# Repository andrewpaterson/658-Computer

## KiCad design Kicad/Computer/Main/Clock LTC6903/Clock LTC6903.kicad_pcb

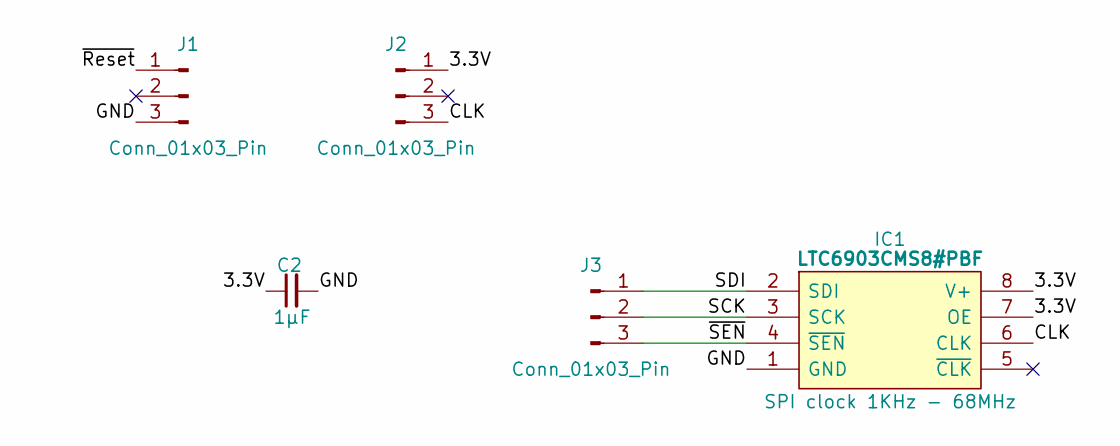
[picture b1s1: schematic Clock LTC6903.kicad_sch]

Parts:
C2: 1μF; C_0805
IC1: LTC6903CMS8#PBF; SOP65P490X110-8N; Manufacturer_Part_Number LTC6903CMS8#PBF
J1, J2, J3: Conn_01x03_Pin; PinHeader_1x03_P2.54mm_Vertical

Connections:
/3.3V: C2.1, IC1.7 (OE), IC1.8 (V+), J2.1
/CLK: IC1.6 (CLK), J2.3
/GND: C2.2, IC1.1 (GND), J1.3
/SCK: IC1.3 (SCK), J3.2
/SDI: IC1.2 (SDI), J3.1
/~Reset: J1.1
/~SEN: IC1.4 (~SEN), J3.3

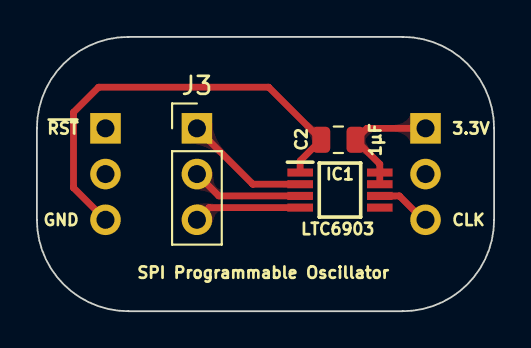
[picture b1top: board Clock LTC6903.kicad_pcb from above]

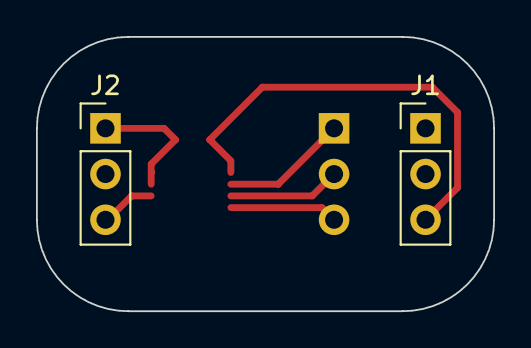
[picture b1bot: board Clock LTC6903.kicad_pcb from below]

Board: 2 copper layers, 25.4 x 15.2 mm, 5 parts (2 on the bottom side), 6 nets.

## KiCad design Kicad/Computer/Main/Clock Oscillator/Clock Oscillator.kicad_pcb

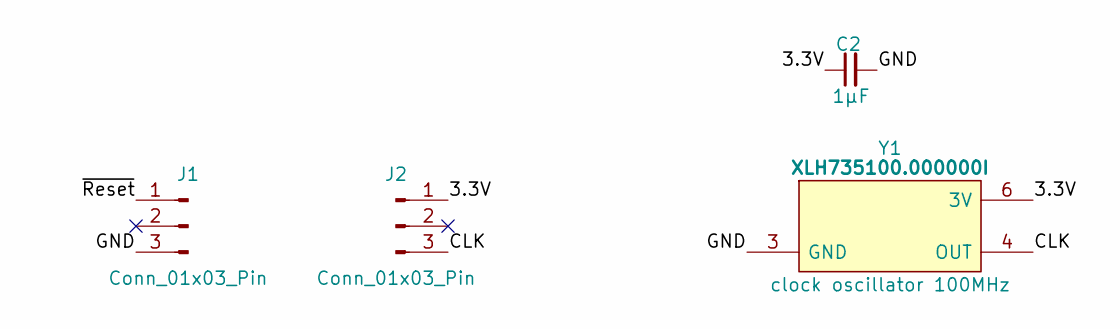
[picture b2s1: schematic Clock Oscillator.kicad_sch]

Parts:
C2: 1μF; C_0805
J1, J2: Conn_01x03_Pin; PinHeader_1x03_P2.54mm_Vertical
Y1: XLH735100.000000I; XLH735100000000I; Mouser Part Number 972-XLH735100000000I

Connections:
/3.3V: C2.1, J2.1, Y1.6 (3V)
/CLK: J2.3, Y1.4 (OUT)
/GND: C2.2, J1.3, Y1.3 (GND)
/~Reset: J1.1

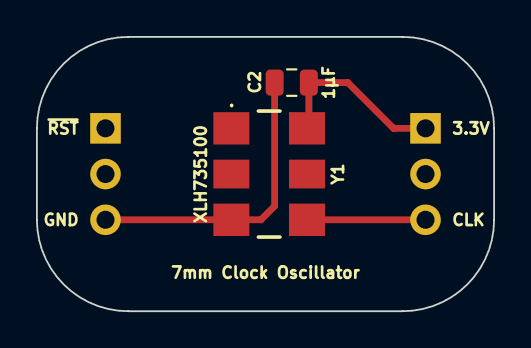
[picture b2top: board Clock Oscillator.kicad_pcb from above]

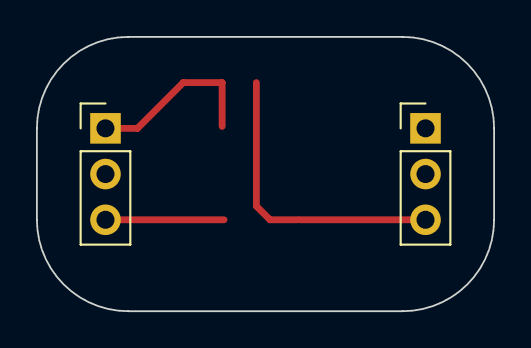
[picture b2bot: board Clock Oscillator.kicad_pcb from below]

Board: 2 copper layers, 25.4 x 15.2 mm, 4 parts (2 on the bottom side), 3 nets.

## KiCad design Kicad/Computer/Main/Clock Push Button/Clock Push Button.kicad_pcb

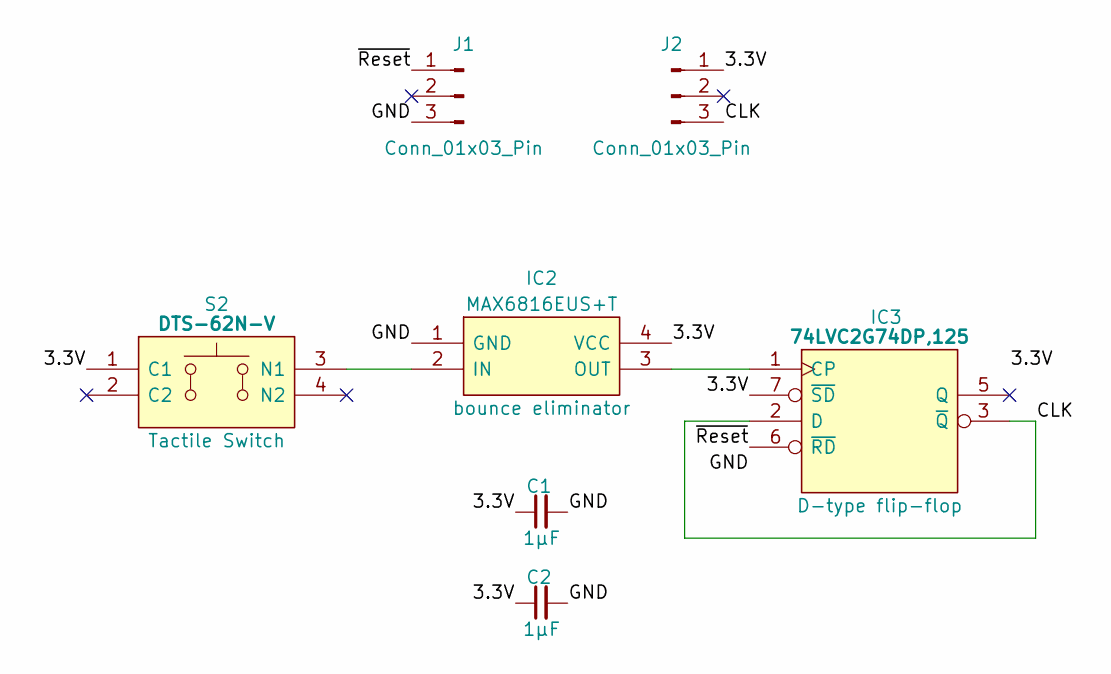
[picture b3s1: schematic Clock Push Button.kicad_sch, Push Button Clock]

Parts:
C1, C2: 1μF; C_0805
IC2: MAX6816EUS+T; MAX812REUST; Manufacturer_Part_Number MAX6816EUS+T; Mouser Part Number 700-MAX6816EUST
IC3: 74LVC2G74DP,125; SOP65P400X110-8N; Manufacturer_Part_Number 74LVC2G74DP,125; Mouser Part Number 771-74LVC2G74DP-G
J1, J2: Conn_01x03_Pin; PinHeader_1x03_P2.54mm_Vertical
S2: DTS-62N-V; DTS62NV; Manufacturer_Part_Number DTS-62N-V; Mouser Part Number 113-DTS-62N-V

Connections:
/3.3V: C1.1, C2.1, IC2.4 (VCC), IC3.7 (~SD), IC3.8 (3V), J2.1, S2.1 (C1)
/CLK: IC3.2 (D), IC3.3 (~Q), J2.3
/GND: C1.2, C2.2, IC2.1 (GND), IC3.4 (GND), J1.3
/~Reset: IC3.6 (~RD), J1.1
unnamed: IC2.2 (IN), S2.3 (N1)
unnamed: IC2.3 (OUT), IC3.1 (CP)

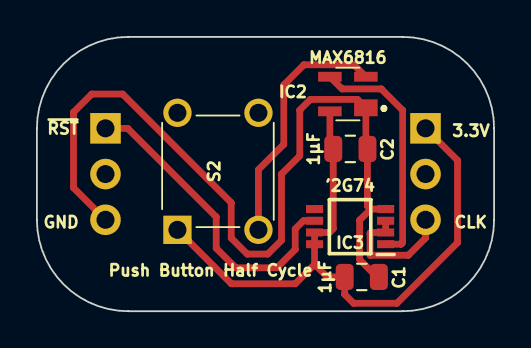
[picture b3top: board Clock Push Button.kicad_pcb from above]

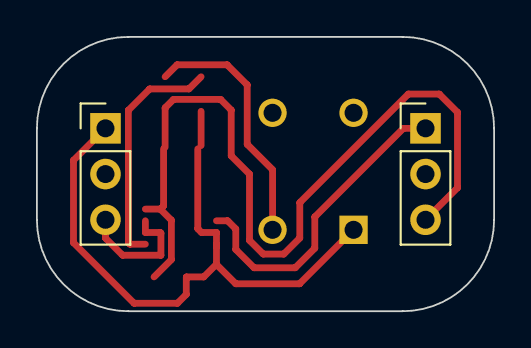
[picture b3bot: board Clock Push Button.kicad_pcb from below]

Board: 2 copper layers, 25.4 x 15.2 mm, 7 parts (2 on the bottom side), 6 nets.

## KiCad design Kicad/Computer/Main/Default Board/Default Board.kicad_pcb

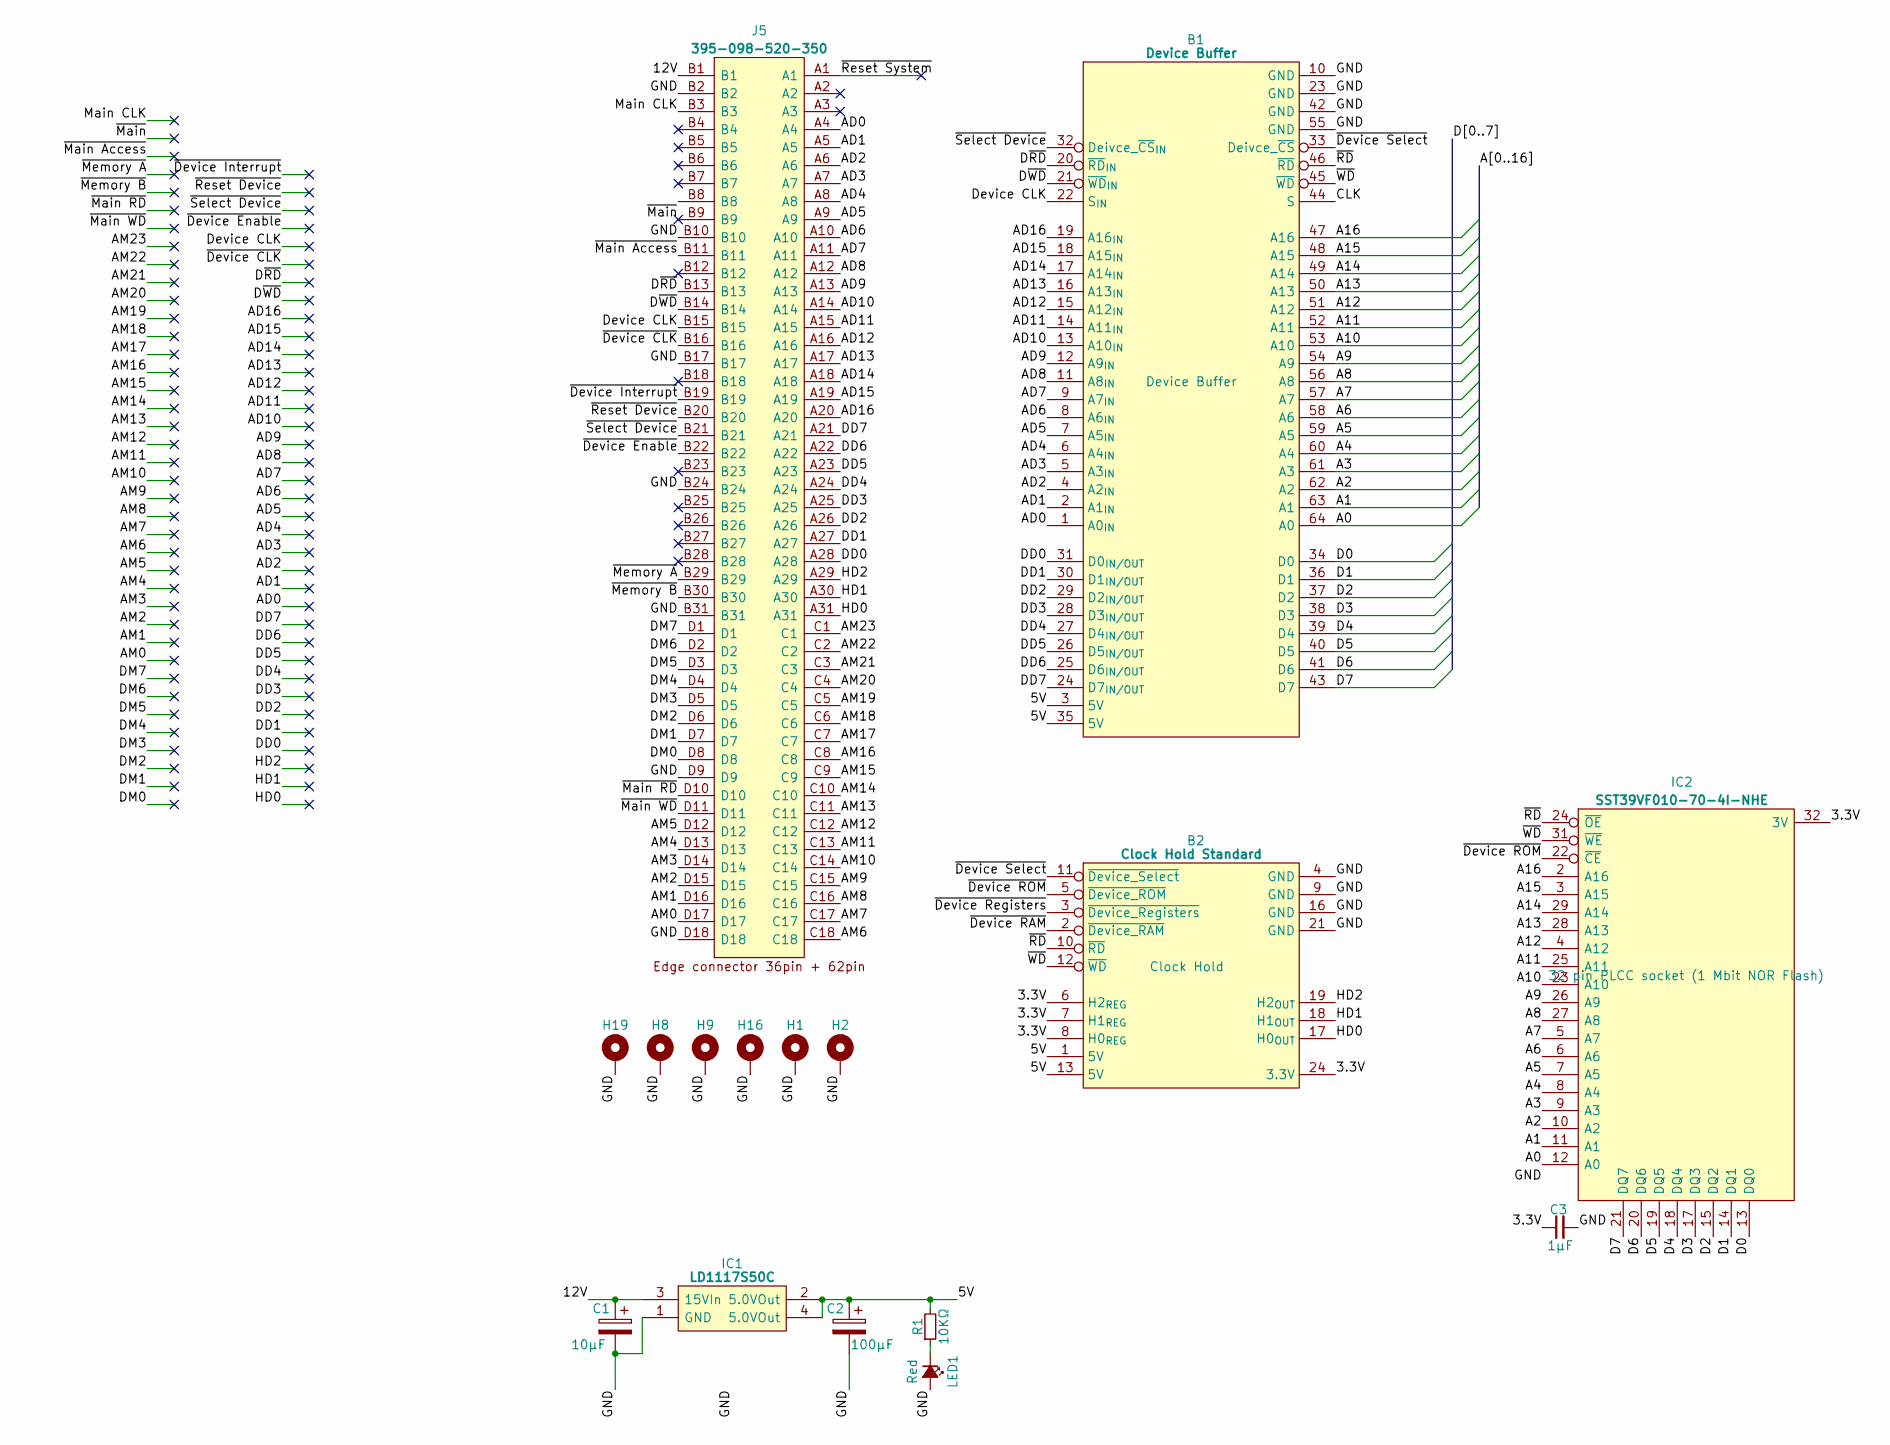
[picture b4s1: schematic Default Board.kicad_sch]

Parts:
B1: Device Buffer; HCP65_Device_Buffer
B2: Clock Hold Standard; HCP65_Clock_Hold_Standard
C1: 10μF; CP_Radial_D4.0mm_P2.00mm
C2: 100μF; CP_Radial_D4.0mm_P2.00mm
C3: 1μF; C_0805
H1, H2, H8, H9, H16, H19: MountingHole_Pad; HCP65_MountingHole_M3_
IC1: LD1117S50C; LD1117S33C; Manufacturer_Part_Number LD1117S50C
IC2: SST39VF010-70-4I-NHE; 5408803224008; Manufacturer_Part_Number SST39VF010-70-4I-NHE
J5: 395-098-520-350; 98pin Edge Connector; Manufacturer_Part_Number 395-098-520-350; Mouser Part Number 587-395-098-520-350
LED1: Red; LED_D5.0mm
R1: 10KΩ; R_0805

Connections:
/3.3V: B2.6 (H2_{REG}), B2.7 (H1_{REG}), B2.8 (H0_{REG}), B2.24 (3.3V), C3.1, IC2.32 (3V)
/5V: B1.3 (5V), B1.35 (5V), B2.1 (5V), B2.13 (5V), C2.1, IC1.2 (5.0VOut), IC1.4 (5.0VOut), R1.2
/12V: C1.1, IC1.3 (15VIn), J5.B1
/A0: B1.64 (A0), IC2.12 (A0)
/A0_{D}: B1.1 (A0_{IN}), J5.A4
/A1: B1.63 (A1), IC2.11 (A1)
/A1_{D}: B1.2 (A1_{IN}), J5.A5
/A2: B1.62 (A2), IC2.10 (A2)
/A2_{D}: B1.4 (A2_{IN}), J5.A6
/A3: B1.61 (A3), IC2.9 (A3)
/A3_{D}: B1.5 (A3_{IN}), J5.A7
/A4: B1.60 (A4), IC2.8 (A4)
/A4_{D}: B1.6 (A4_{IN}), J5.A8
/A5: B1.59 (A5), IC2.7 (A5)
/A5_{D}: B1.7 (A5_{IN}), J5.A9
/A6: B1.58 (A6), IC2.6 (A6)
/A6_{D}: B1.8 (A6_{IN}), J5.A10
/A7: B1.57 (A7), IC2.5 (A7)
/A7_{D}: B1.9 (A7_{IN}), J5.A11
/A8: B1.56 (A8), IC2.27 (A8)
/A8_{D}: B1.11 (A8_{IN}), J5.A12
/A9: B1.54 (A9), IC2.26 (A9)
/A9_{D}: B1.12 (A9_{IN}), J5.A13
/A10: B1.53 (A10), IC2.23 (A10)
/A10_{D}: B1.13 (A10_{IN}), J5.A14
/A11: B1.52 (A11), IC2.25 (A11)
/A11_{D}: B1.14 (A11_{IN}), J5.A15
/A12: B1.51 (A12), IC2.4 (A12)
/A12_{D}: B1.15 (A12_{IN}), J5.A16
/A13: B1.50 (A13), IC2.28 (A13)
/A13_{D}: B1.16 (A13_{IN}), J5.A17
/A14: B1.49 (A14), IC2.29 (A14)
/A14_{D}: B1.17 (A14_{IN}), J5.A18
/A15: B1.48 (A15), IC2.3 (A15)
/A15_{D}: B1.18 (A15_{IN}), J5.A19
/A16: B1.47 (A16), IC2.2 (A16)
/A16_{D}: B1.19 (A16_{IN}), J5.A20
/AM0: J5.D17
/AM1: J5.D16
/AM2: J5.D15
/AM3: J5.D14
/AM4: J5.D13
/AM5: J5.D12
/AM6: J5.C18
/AM7: J5.C17
/AM8: J5.C16
/AM9: J5.C15
/AM10: J5.C14
/AM11: J5.C13
/AM12: J5.C12
/AM13: J5.C11
/AM14: J5.C10
/AM15: J5.C9
/AM16: J5.C8
/AM17: J5.C7
/AM18: J5.C6
/AM19: J5.C5
/AM20: J5.C4
/AM21: J5.C3
/AM22: J5.C2
/AM23: J5.C1
/CLK: B1.44 (S)
/CLK_{D}: B1.22 (S_{IN}), J5.B15
/CLK_{M}: J5.B3
/D0: B1.34 (D0), IC2.13 (DQ0)
/D0_{D}: B1.31 (D0_{IN/OUT}), J5.A28
/D1: B1.36 (D1), IC2.14 (DQ1)
/D1_{D}: B1.30 (D1_{IN/OUT}), J5.A27
/D2: B1.37 (D2), IC2.15 (DQ2)
/D2_{D}: B1.29 (D2_{IN/OUT}), J5.A26
/D3: B1.38 (D3), IC2.17 (DQ3)
/D3_{D}: B1.28 (D3_{IN/OUT}), J5.A25
/D4: B1.39 (D4), IC2.18 (DQ4)
/D4_{D}: B1.27 (D4_{IN/OUT}), J5.A24
/D5: B1.40 (D5), IC2.19 (DQ5)
/D5_{D}: B1.26 (D5_{IN/OUT}), J5.A23
/D6: B1.41 (D6), IC2.20 (DQ6)
/D6_{D}: B1.25 (D6_{IN/OUT}), J5.A22
/D7: B1.43 (D7), IC2.21 (DQ7)
/D7_{D}: B1.24 (D7_{IN/OUT}), J5.A21
/DM0: J5.D8
/DM1: J5.D7
/DM2: J5.D6
/DM3: J5.D5
/DM4: J5.D4
/DM5: J5.D3
/DM6: J5.D2
/DM7: J5.D1
/GND: B1.10 (GND), B1.23 (GND), B1.42 (GND), B1.55 (GND), B2.4 (GND), B2.9 (GND), B2.16 (GND), B2.21 (GND), C1.2, C2.2, C3.2, H1.1 (GND), H2.1 (GND), H8.1 (GND), H9.1 (GND), H16.1 (GND), H19.1 (GND), IC1.1 (GND), IC2.16 (GND), J5.B2, J5.B10, J5.B17, J5.B24, J5.B31, J5.D9, J5.D18, LED1.2 (A)
/H0_{D}: B2.17 (H0_{OUT}), J5.A31
/H1_{D}: B2.18 (H1_{OUT}), J5.A30
/H2_{D}: B2.19 (H2_{OUT}), J5.A29
/~CLK_{D}: J5.B16
/~Device RAM: B2.2 (~Device_RAM)
/~Device ROM: B2.5 (~Device_ROM), IC2.22 (~CE)
/~Device Registers: B2.3 (~Device_Registers)
/~Device Select: B1.33 (Deivce_~CS), B2.11 (~Device_Select)
/~Enable_{D}: J5.B22
/~Interrupt_{D}: J5.B19
/~Main Access: J5.B11
/~Main: J5.B9
/~Memory A: J5.B29
/~Memory B: J5.B30
/~RD: B1.46 (~RD), B2.10 (~RD), IC2.24 (~OE)
/~RD_{D}: B1.20 (~RD_{IN}), J5.B13
/~RD_{M}: J5.D10
/~Reset_{D}: J5.B20
/~Reset_{System}: J5.A1
/~Select_{D}: B1.32 (Deivce_~CS_{IN}), J5.B21
/~WD: B1.45 (~WD), B2.12 (~WD), IC2.31 (~WE)
/~WD_{D}: B1.21 (~WD_{IN}), J5.B14
/~WD_{M}: J5.D11
unnamed: LED1.1 (K), R1.1

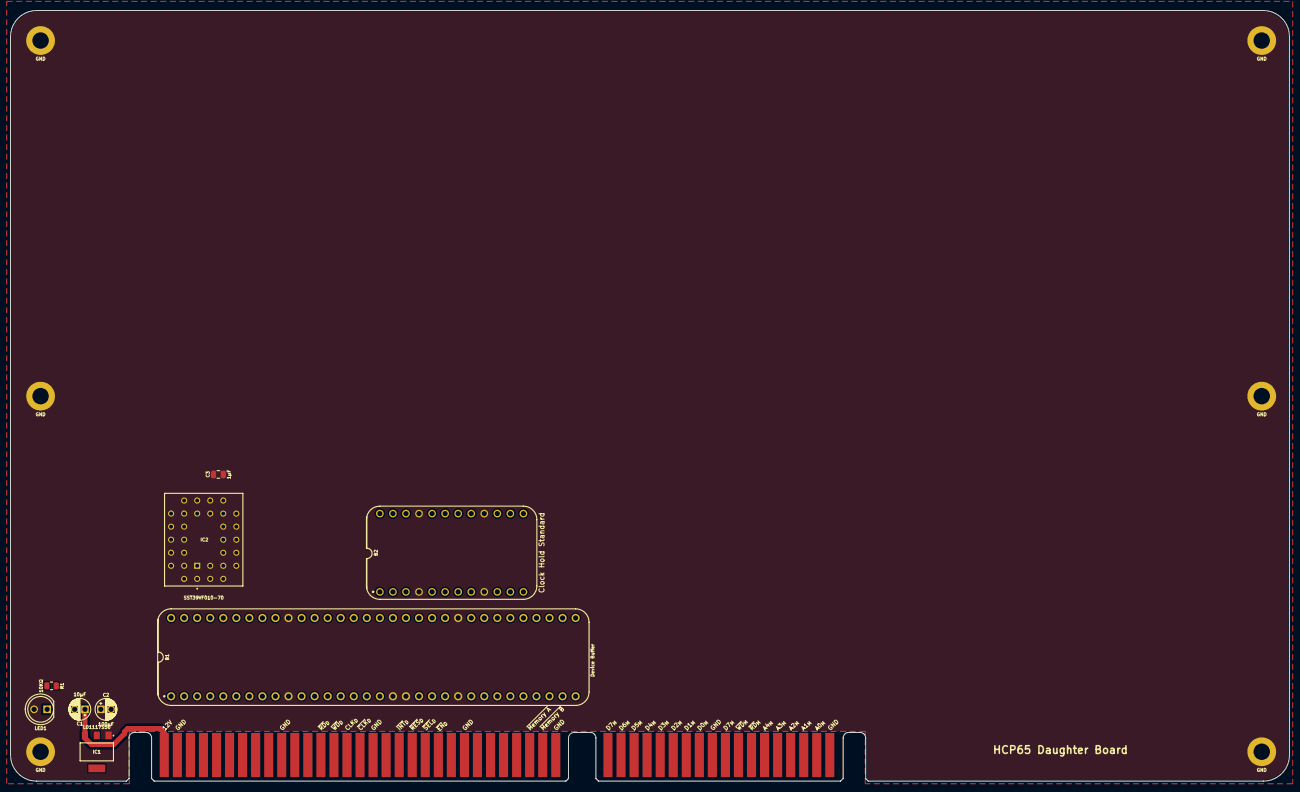
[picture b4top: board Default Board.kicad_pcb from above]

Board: 2 copper layers, 248.9 x 150.0 mm, 16 parts (0 on the bottom side), 66 nets.

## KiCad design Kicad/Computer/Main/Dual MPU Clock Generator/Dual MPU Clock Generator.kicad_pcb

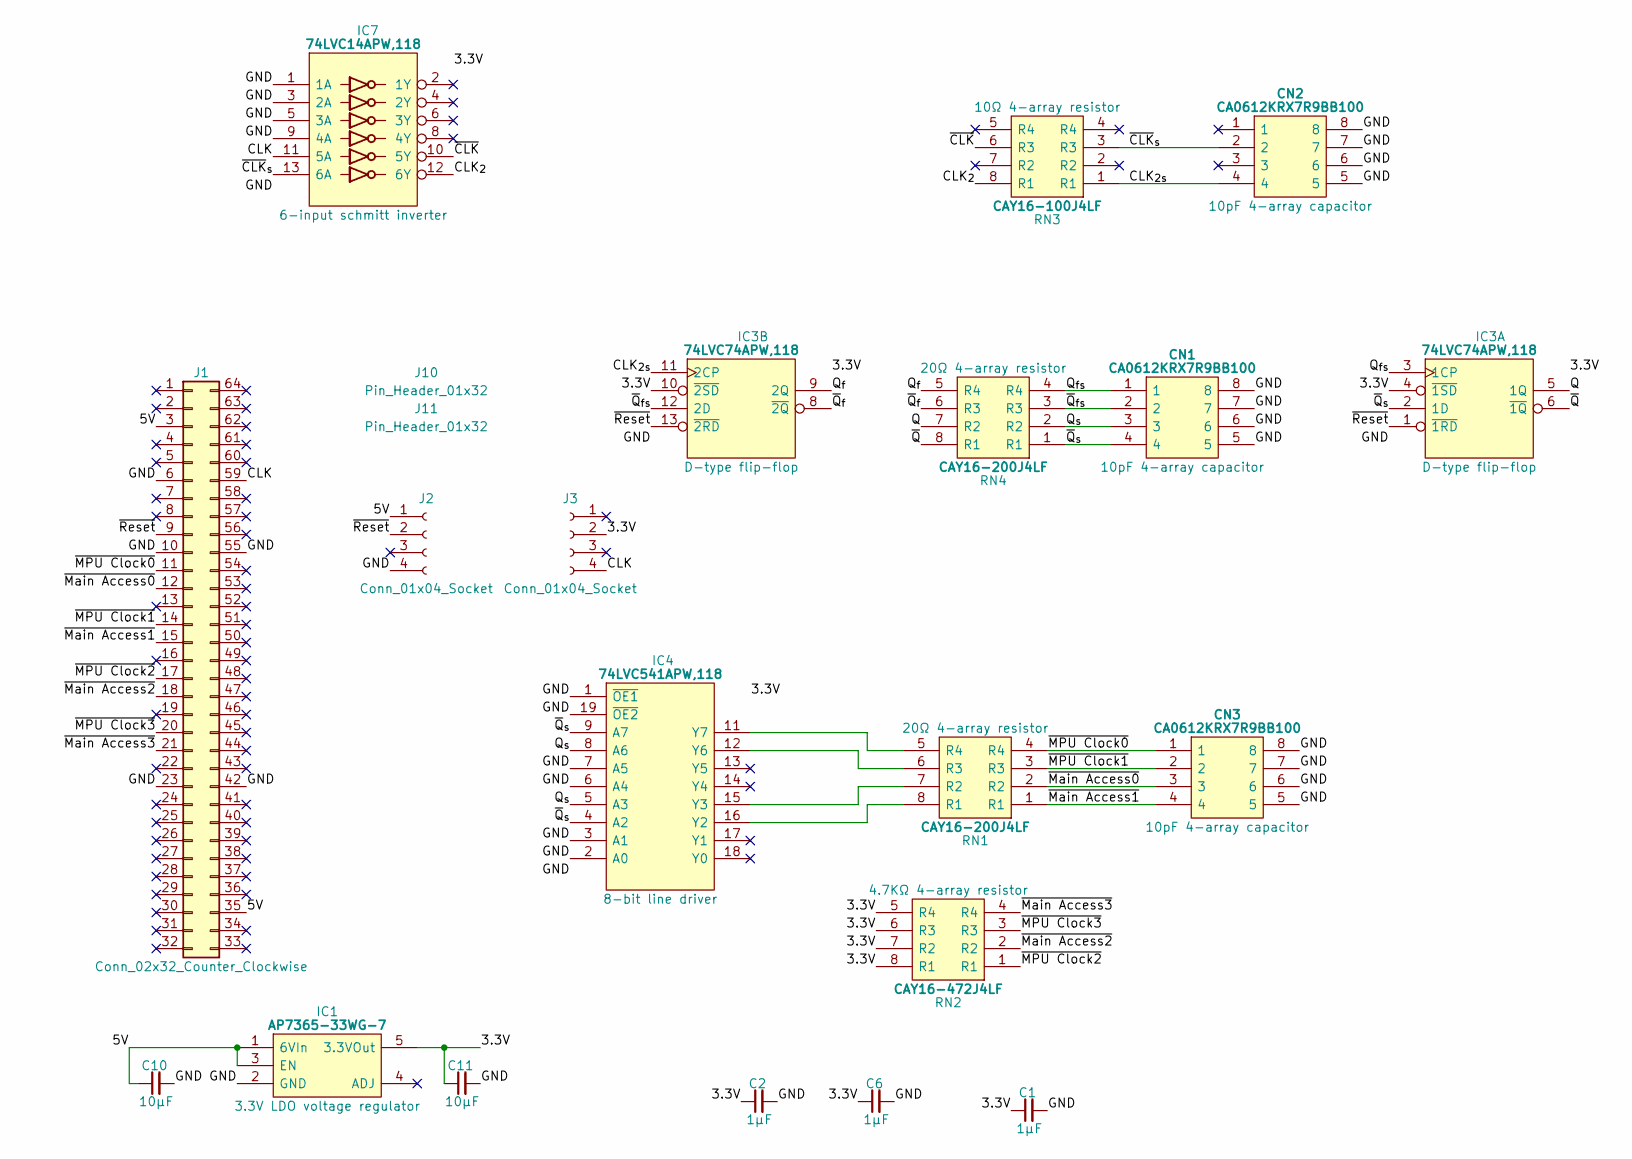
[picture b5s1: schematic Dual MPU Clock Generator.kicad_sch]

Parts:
C1, C2, C6: 1μF; C_0805
C10, C11: 10µF; C_0805
CN1, CN2, CN3: CA0612KRX7R9BB100; Manufacturer_Part_Number CA0612KRX7R9BB102; Mouser Part Number 603-CA612KRX7R9BB102
IC1: AP7365-33WG-7; SOT95P285X130-5N; Manufacturer_Part_Number AP7365-33WG-7; Mouser Part Number 621-AP7365-33WG-7
IC3: 74LVC74APW,118; SOP65P640X110-14N; Mouser Part Number 771-74LVC74APW-T
IC4: 74LVC541APW,118; SOP65P640X110-20N; Mouser Part Number 771-74LVC541APW-T
IC7: 74LVC14APW,118; SOP65P640X110-14N; Manufacturer_Part_Number 74LVC14APW,118; Mouser Part Number 771-74LVC14APW-T
J1: Conn_02x32_Counter_Clockwise; DIP-64_Board_W22.86mm
J2, J3: Conn_01x04_Socket; PinSocket_1x04_P2.54mm_Vertical
J10, J11: Pin_Header_01x32; PinHeader_1x32_P2.54mm_Vertical
RN1, RN4: CAY16-200J4LF; CAY16-F4; Manufacturer_Part_Number CAY16-331J4LF; Mouser Part Number 652-CAY16-331J4LF
RN2: CAY16-472J4LF; CAY16-F4; Manufacturer_Part_Number CAY16-472J4LF; Mouser Part Number 652-CAY16-472J4LF
RN3: CAY16-100J4LF; CAY16-F4; Manufacturer_Part_Number CAY16-331J4LF; Mouser Part Number 652-CAY16-331J4LF

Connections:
/3.3V: C1.1, C2.1, C6.1, C11.1, IC1.5 (3.3VOut), IC3.4 (~1SD), IC3.10 (~2SD), IC3.14 (3V), IC4.20 (3V), IC7.14 (3V), J3.2, RN2.5 (R4), RN2.6 (R3), RN2.7 (R2), RN2.8 (R1)
/5V: C10.1, IC1.1 (6VIn), IC1.3 (EN), J1.3, J1.35, J2.1
/CLK: IC7.11 (5A), J1.59, J3.4
/CLK_{2s}: CN2.4, IC3.11 (2CP), RN3.1 (R1)
/CLK_{2}: IC7.12 (6Y), RN3.8 (R1)
/GND: C1.2, C2.2, C6.2, C10.2, C11.2, CN1.5, CN1.6, CN1.7, CN1.8, CN2.5, CN2.6, CN2.7, CN2.8, CN3.5, CN3.6, CN3.7, CN3.8, IC1.2 (GND), IC3.7 (GND), IC4.1 (~OE1), IC4.2 (A0), IC4.3 (A1), IC4.6 (A4), IC4.7 (A5), IC4.10 (GND), IC4.19 (~OE2), IC7.1 (1A), IC7.3 (2A), IC7.5 (3A), IC7.7 (GND), IC7.9 (4A), J1.6, J1.10, J1.23, J1.42, J1.55, J2.4
/Q: IC3.5 (1Q), RN4.7 (R2)
/Q_{fs}: CN1.1, IC3.3 (1CP), RN4.4 (R4)
/Q_{f}: IC3.9 (2Q), RN4.5 (R4)
/Q_{s}: CN1.3, IC4.5 (A3), IC4.8 (A6), RN4.2 (R2)
/~CLK: IC7.10 (5Y), RN3.6 (R3)
/~CLK_{s}: CN2.2, IC7.13 (6A), RN3.3 (R3)
/~MPU Clock0: CN3.1, J1.11, RN1.4 (R4)
/~MPU Clock1: CN3.2, J1.14, RN1.3 (R3)
/~MPU Clock2: J1.17, RN2.1 (R1)
/~MPU Clock3: J1.20, RN2.3 (R3)
/~Main Access0: CN3.3, J1.12, RN1.2 (R2)
/~Main Access1: CN3.4, J1.15, RN1.1 (R1)
/~Main Access2: J1.18, RN2.2 (R2)
/~Main Access3: J1.21, RN2.4 (R4)
/~Q: IC3.6 (~1Q), RN4.8 (R1)
/~Q_{fs}: CN1.2, IC3.12 (2D), RN4.3 (R3)
/~Q_{f}: IC3.8 (~2Q), RN4.6 (R3)
/~Q_{s}: CN1.4, IC3.2 (1D), IC4.4 (A2), IC4.9 (A7), RN4.1 (R1)
/~Reset: IC3.1 (~1RD), IC3.13 (~2RD), J1.9, J2.2
unnamed: IC4.16 (Y2), RN1.8 (R1)
unnamed: IC4.15 (Y3), RN1.7 (R2)
unnamed: IC4.12 (Y6), RN1.6 (R3)
unnamed: IC4.11 (Y7), RN1.5 (R4)

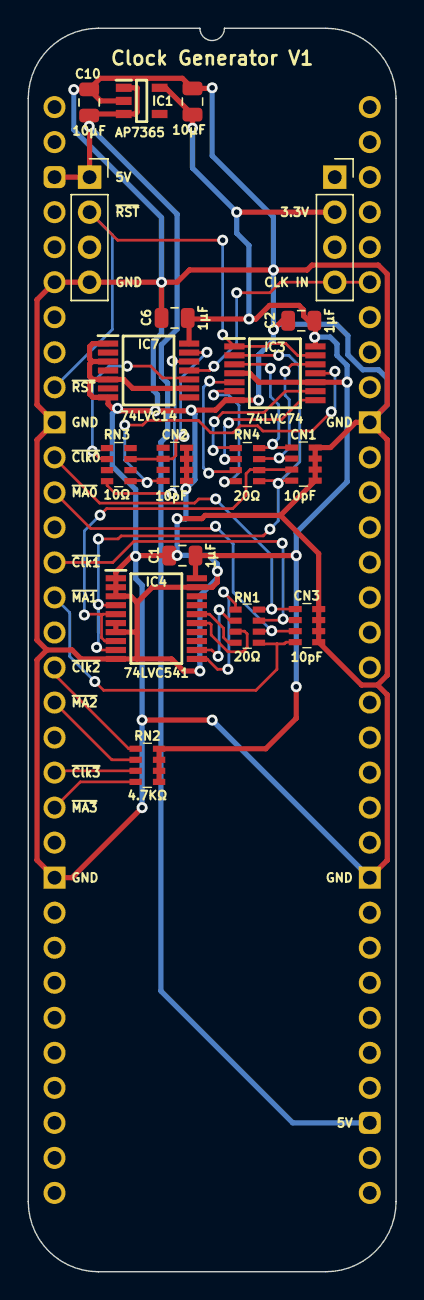
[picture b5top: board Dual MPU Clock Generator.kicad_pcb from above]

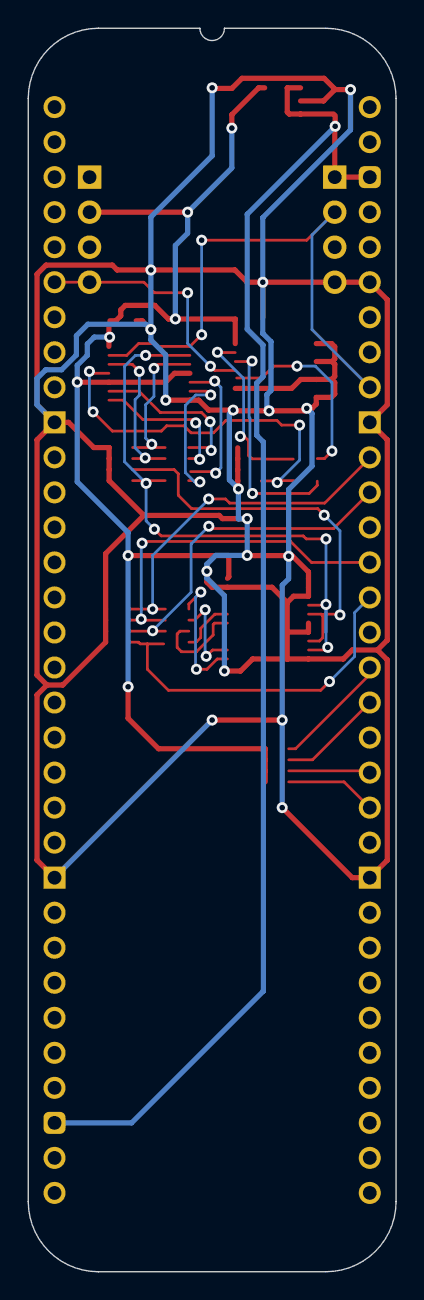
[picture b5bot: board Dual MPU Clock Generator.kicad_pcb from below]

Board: 2 copper layers, 26.7 x 90.2 mm, 21 parts (2 on the bottom side), 29 nets.

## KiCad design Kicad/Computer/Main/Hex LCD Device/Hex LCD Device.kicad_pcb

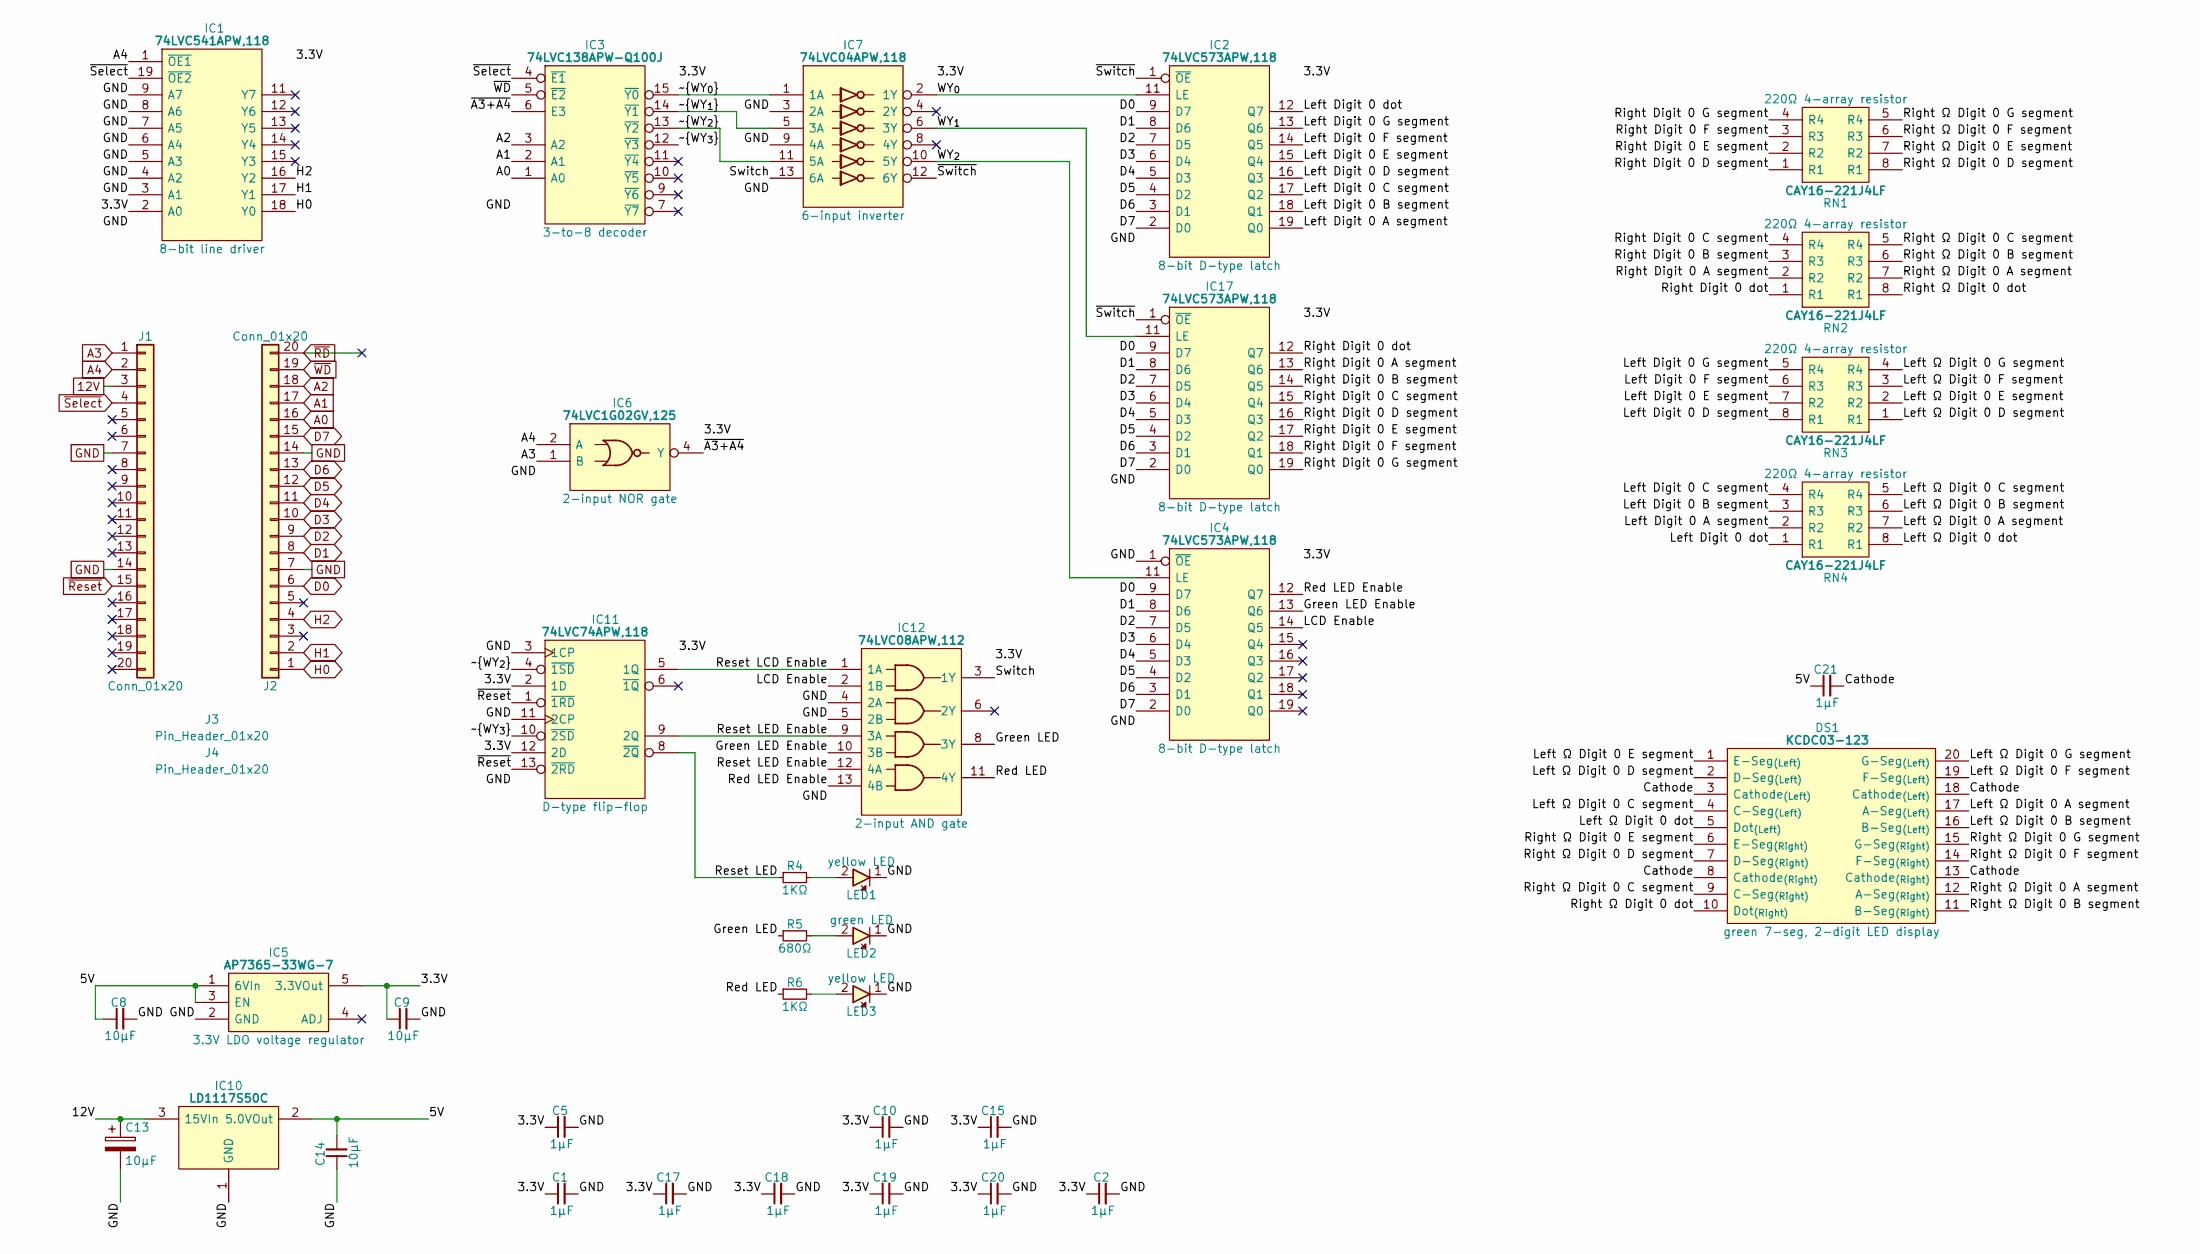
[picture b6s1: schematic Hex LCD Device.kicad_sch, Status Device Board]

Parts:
C1, C2, C5, C10, C15, C17, C18, C19, C20: 1μF; C_0805
C8, C9, C14: 10µF; C_0805
C13: 10μF; CP_Radial_D5.0mm_P2.00mm
C21: 1µF; C_0805
DS1: KCDC03-123; KCDC03123; Manufacturer_Part_Number KCDC03-123; Mouser Part Number N/A
IC1: 74LVC541APW,118; SOP65P640X110-20N; Mouser Part Number 771-74LVC541APW-T
IC2, IC4, IC17: 74LVC573APW,118; SOP65P640X110-20N; Mouser Part Number 771-74LVC573APW-T
IC3: 74LVC138APW-Q100J; SOP65P640X110-16N; Mouser Part Number 771-74LVC138APWQ100J
IC5: AP7365-33WG-7; SOT95P285X130-5N; Manufacturer_Part_Number AP7365-33WG-7; Mouser Part Number 621-AP7365-33WG-7
IC6: 74LVC1G02GV,125; SOT95P275X110-5N; Manufacturer_Part_Number 74LVC1G02GV,125; Mouser Part Number 771-LVC1G02GV125
IC7: 74LVC04APW,118; SOP65P640X110-14N; Manufacturer_Part_Number 74LVC04APW,118; Mouser Part Number 771-74LVC04APW-T
IC10: LD1117S50C; LD1117S33C; Manufacturer_Part_Number LD1117S50C
IC11: 74LVC74APW,118; SOP65P640X110-14N; Mouser Part Number 771-74LVC74APW-T
IC12: 74LVC08APW,112; SOP65P640X110-14N; Manufacturer_Part_Number 74LVC08APW,112; Mouser Part Number 771-74LVC08APW
J1, J2: Conn_01x20; SIP_20_Pins
J3, J4: Pin_Header_01x20; PinHeader_1x20_P2.54mm_Vertical
LED1, LED3: 150224YS73100A; 150224BS73100A
LED2: 150224VS73100A; Manufacturer_Part_Number 150224VS73100A; Mouser Part Number 710-150224VS73100A
R4, R6: 1KΩ; R_0805
R5: 680Ω; R_0805
RN1, RN2, RN3, RN4: CAY16-221J4LF; CAY16-F4; Manufacturer_Part_Number CAY16-221J4LF; Mouser Part Number 652-CAY16-221J4LF

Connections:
12V: C13.1, IC10.3 (15VIn), J1.3
/3.3V: C1.1, C2.1, C5.1, C9.1, C10.1, C15.1, C17.1, C18.1, C19.1, C20.1, IC1.2 (A0), IC1.20 (3V), IC2.20 (3V), IC3.16 (3V), IC4.20 (3V), IC5.5 (3.3VOut), IC6.5 (3V), IC7.14 (3V), IC11.2 (1D), IC11.12 (2D), IC11.14 (3V), IC12.14 (3V), IC17.20 (3V)
/5V: C8.1, C14.2, C21.1, IC5.1 (6VIn), IC5.3 (EN), IC10.2 (5.0VOut)
/Cathode: C21.2, DS1.3 (Cathode_{(Left)}), DS1.8 (Cathode_{(Right)}), DS1.13 (Cathode_{(Right)}), DS1.18 (Cathode_{(Left)})
/Green LED: IC12.8 (3Y), R5.1
/Green LED Enable: IC4.13 (Q6), IC12.10 (3B)
/LCD Enable: IC4.14 (Q5), IC12.2 (1B)
/Left Digit 0 A segment: IC2.19 (Q0), RN4.2 (R2)
/Left Digit 0 B segment: IC2.18 (Q1), RN4.3 (R3)
/Left Digit 0 C segment: IC2.17 (Q2), RN4.4 (R4)
/Left Digit 0 D segment: IC2.16 (Q3), RN3.8 (R1)
/Left Digit 0 E segment: IC2.15 (Q4), RN3.7 (R2)
/Left Digit 0 F segment: IC2.14 (Q5), RN3.6 (R3)
/Left Digit 0 G segment: IC2.13 (Q6), RN3.5 (R4)
/Left Digit 0 dot: IC2.12 (Q7), RN4.1 (R1)
/Left Ω Digit 0 A segment: DS1.17 (A-Seg_{(Left)}), RN4.7 (R2)
/Left Ω Digit 0 B segment: DS1.16 (B-Seg_{(Left)}), RN4.6 (R3)
/Left Ω Digit 0 C segment: DS1.4 (C-Seg_{(Left)}), RN4.5 (R4)
/Left Ω Digit 0 D segment: DS1.2 (D-Seg_{(Left)}), RN3.1 (R1)
/Left Ω Digit 0 E segment: DS1.1 (E-Seg_{(Left)}), RN3.2 (R2)
/Left Ω Digit 0 F segment: DS1.19 (F-Seg_{(Left)}), RN3.3 (R3)
/Left Ω Digit 0 G segment: DS1.20 (G-Seg_{(Left)}), RN3.4 (R4)
/Left Ω Digit 0 dot: DS1.5 (Dot_{(Left)}), RN4.8 (R1)
/Red LED: IC12.11 (4Y), R6.1
/Red LED Enable: IC4.12 (Q7), IC12.13 (4B)
/Reset LCD Enable: IC11.5 (1Q), IC12.1 (1A)
/Reset LED: IC11.8 (~2Q), R4.1
/Reset LED Enable: IC11.9 (2Q), IC12.9 (3A), IC12.12 (4A)
/Right Digit 0 A segment: IC17.13 (Q6), RN2.2 (R2)
/Right Digit 0 B segment: IC17.14 (Q5), RN2.3 (R3)
/Right Digit 0 C segment: IC17.15 (Q4), RN2.4 (R4)
/Right Digit 0 D segment: IC17.16 (Q3), RN1.1 (R1)
/Right Digit 0 E segment: IC17.17 (Q2), RN1.2 (R2)
/Right Digit 0 F segment: IC17.18 (Q1), RN1.3 (R3)
/Right Digit 0 G segment: IC17.19 (Q0), RN1.4 (R4)
/Right Digit 0 dot: IC17.12 (Q7), RN2.1 (R1)
/Right Ω Digit 0 A segment: DS1.12 (A-Seg_{(Right)}), RN2.7 (R2)
/Right Ω Digit 0 B segment: DS1.11 (B-Seg_{(Right)}), RN2.6 (R3)
/Right Ω Digit 0 C segment: DS1.9 (C-Seg_{(Right)}), RN2.5 (R4)
/Right Ω Digit 0 D segment: DS1.7 (D-Seg_{(Right)}), RN1.8 (R1)
/Right Ω Digit 0 E segment: DS1.6 (E-Seg_{(Right)}), RN1.7 (R2)
/Right Ω Digit 0 F segment: DS1.14 (F-Seg_{(Right)}), RN1.6 (R3)
/Right Ω Digit 0 G segment: DS1.15 (G-Seg_{(Right)}), RN1.5 (R4)
/Right Ω Digit 0 dot: DS1.10 (Dot_{(Right)}), RN2.8 (R1)
/Switch: IC7.13 (6A), IC12.3 (1Y)
/WY_{0}: IC2.11 (LE), IC7.2 (1Y)
/WY_{1}: IC7.6 (3Y), IC17.11 (LE)
/WY_{2}: IC4.11 (LE), IC7.10 (5Y)
/~A3+A4: IC3.6 (E3), IC6.4 (Y)
/~Switch: IC2.1 (~OE), IC7.12 (6Y), IC17.1 (~OE)
/~WY_{0}: IC3.15 (~Y0), IC7.1 (1A)
/~WY_{1}: IC3.14 (~Y1), IC7.5 (3A)
/~WY_{2}: IC3.13 (~Y2), IC7.11 (5A), IC11.4 (~1SD)
/~WY_{3}: IC3.12 (~Y3), IC11.10 (~2SD)
A0: IC3.1 (A0), J2.16
A1: IC3.2 (A1), J2.17
A2: IC3.3 (A2), J2.18
A3: IC6.1 (B), J1.1
A4: IC1.1 (~OE1), IC6.2 (A), J1.2
D0: IC2.9 (D7), IC4.9 (D7), IC17.9 (D7), J2.6
D1: IC2.8 (D6), IC4.8 (D6), IC17.8 (D6), J2.8
D2: IC2.7 (D5), IC4.7 (D5), IC17.7 (D5), J2.9
D3: IC2.6 (D4), IC4.6 (D4), IC17.6 (D4), J2.10
D4: IC2.5 (D3), IC4.5 (D3), IC17.5 (D3), J2.11
D5: IC2.4 (D2), IC4.4 (D2), IC17.4 (D2), J2.12
D6: IC2.3 (D1), IC4.3 (D1), IC17.3 (D1), J2.13
D7: IC2.2 (D0), IC4.2 (D0), IC17.2 (D0), J2.15
GND: C1.2, C2.2, C5.2, C8.2, C9.2, C10.2, C13.2, C14.1, C15.2, C17.2, C18.2, C19.2, C20.2, IC1.3 (A1), IC1.4 (A2), IC1.5 (A3), IC1.6 (A4), IC1.7 (A5), IC1.8 (A6), IC1.9 (A7), IC1.10 (GND), IC2.10 (GND), IC3.8 (GND), IC4.1 (~OE), IC4.10 (GND), IC5.2 (GND), IC6.3 (GND), IC7.3 (2A), IC7.7 (GND), IC7.9 (4A), IC10.1 (GND), IC11.3 (1CP), IC11.7 (GND), IC11.11 (2CP), IC12.4 (2A), IC12.5 (2B), IC12.7 (GND), IC17.10 (GND), J1.7, J1.14, J2.7, J2.14, LED1.1, LED2.1, LED3.1
H0: IC1.18 (Y0), J2.1
H1: IC1.17 (Y1), J2.2
H2: IC1.16 (Y2), J2.4
unnamed: LED1.2, R4.2
unnamed: LED2.2, R5.2
unnamed: LED3.2, R6.2
~RD: J2.20
~Reset: IC11.1 (~1RD), IC11.13 (~2RD), J1.15
~Select: IC1.19 (~OE2), IC3.4 (~E1), J1.4
~WD: IC3.5 (~E2), J2.19
